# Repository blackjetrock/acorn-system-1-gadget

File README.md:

# Acorn System One Gadget

This is a small gadget that attaches to an Acorn System One. It is a Pico XL RP2350 with 48 GPIOs attached to the
expansion bus of the System One

* 60K of memory. The RP2350 emulates RAM everywhere in the memory space apart from block 0
* Tracing of addresses as code executes. This is a crude trace at the moment, but could be expanded.
* Loading of binary files from SD card into memory. For instance the monitor can be loaded from SD card and run from RAM.
* Snapshot of the entire 64K memory to an SD card file.
* A USB CLI that can drive the gadget
* An OLED display and three keys, these do nothing at the moment.
* Reset from the USB CLI
* Powering of the System One from the USB supply of the Pico. The regulator has to be removed for this to work. Power can
  come from a host computer if the USB CLI is used, or a battery power pack for portability.

On a system 1 you can load a slightly modified COS and BASIC into memory and run it:

The COS is modified to move the 6522 into RAM so that the keyboard can be driven from the USB CLI. The screen is captured by reading screen memory and also emulating som eof the functions of the 6845 CRT controller.

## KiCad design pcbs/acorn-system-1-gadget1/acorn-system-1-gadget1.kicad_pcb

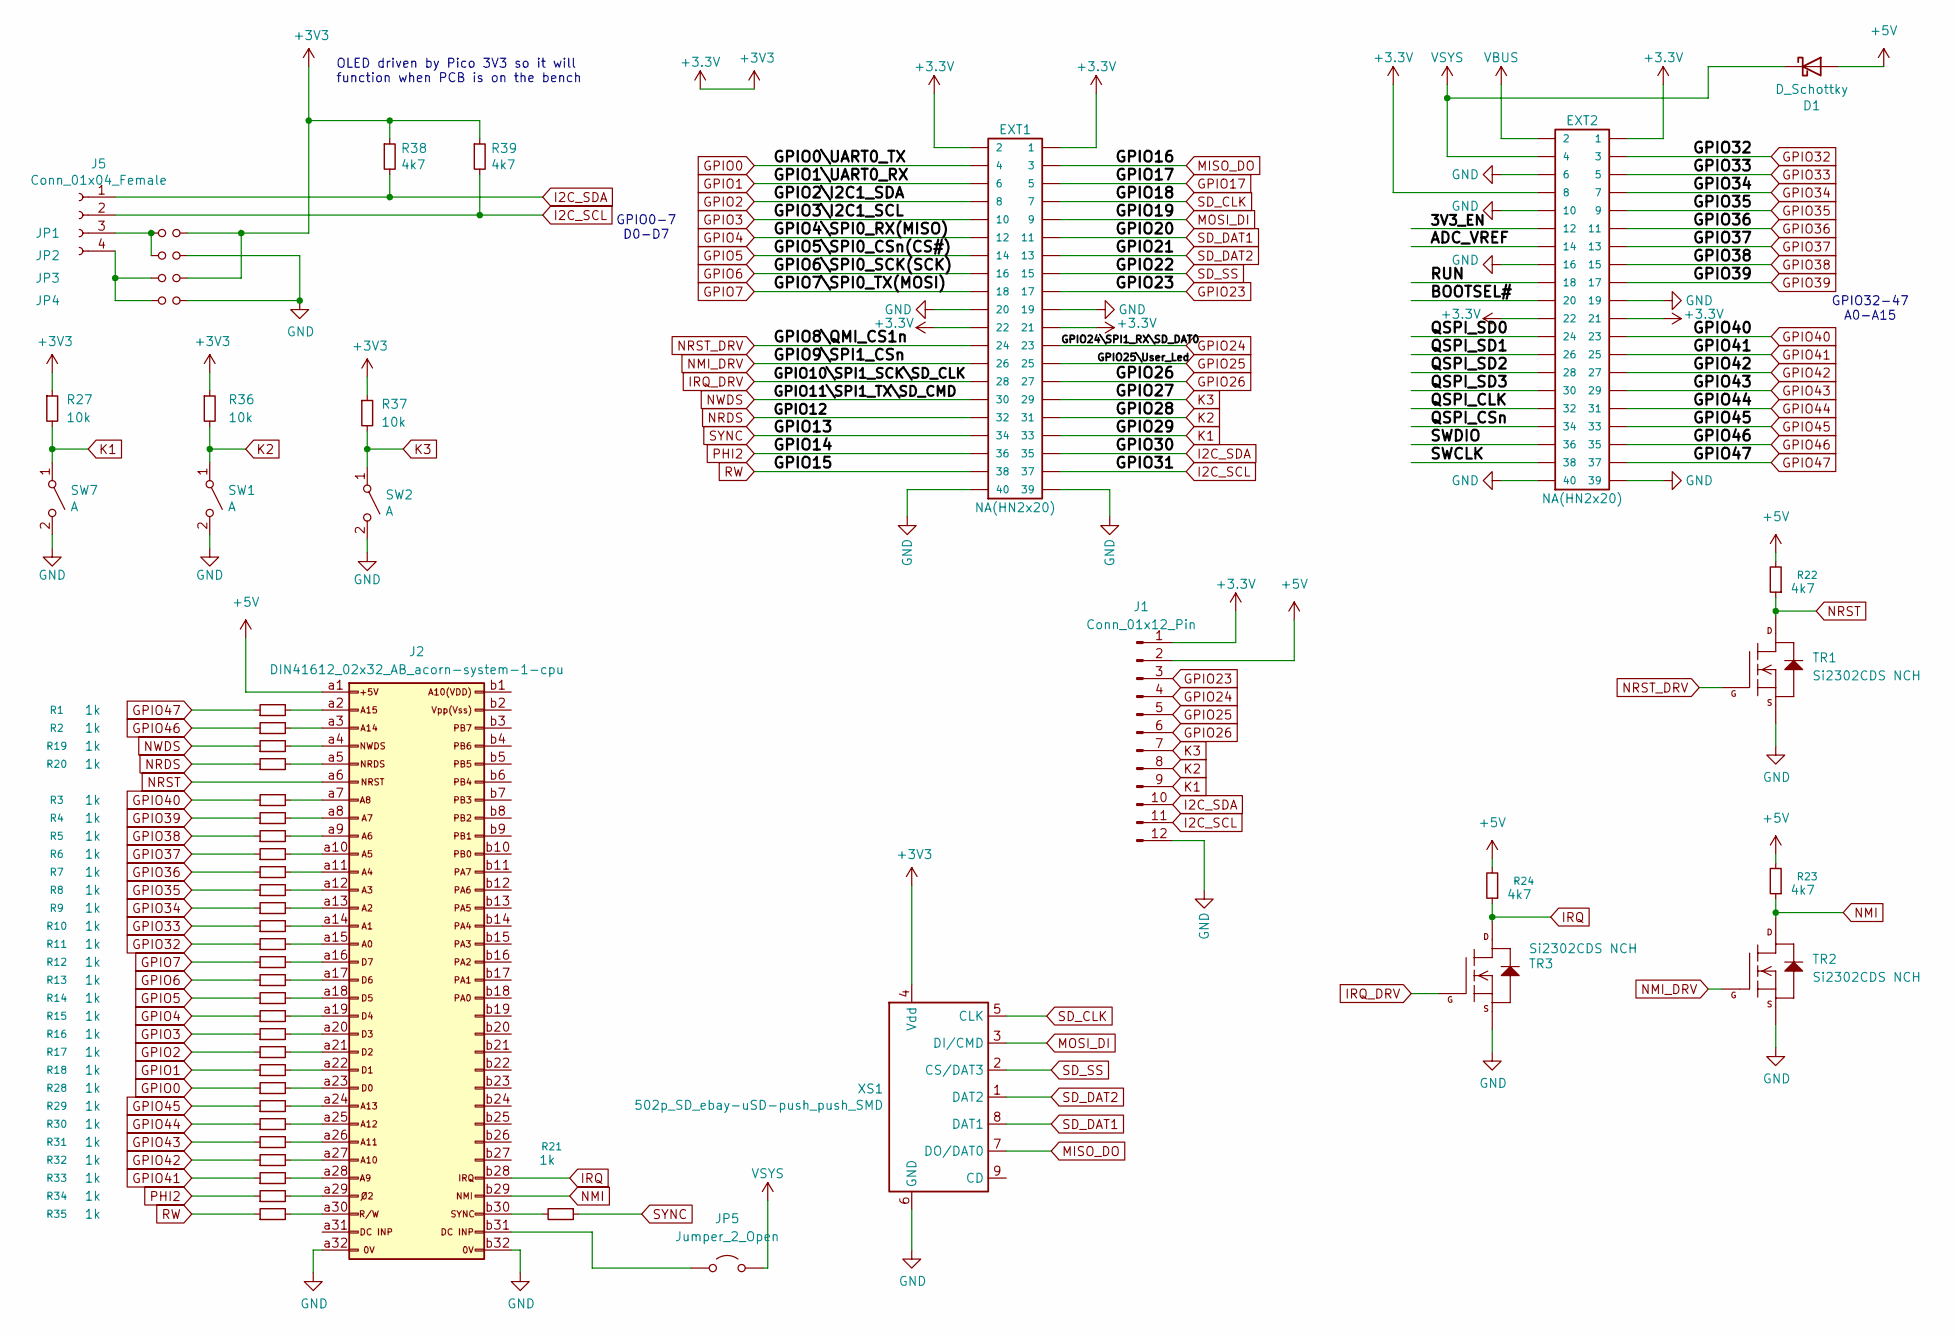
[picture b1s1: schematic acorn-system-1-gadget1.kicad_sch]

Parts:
D1: D_Schottky; D_SOD-123
EXT1, EXT2: NA(HN2x20); PinSocket_2x20_P2.54mm_Vertical
J1: Conn_01x12_Pin; PinHeader_1x12_P2.54mm_Vertical
J2: DIN41612_02x32_AB_acorn-system-1-cpu; DIN41612_Q_2x32_Female_Horizontal_THT
J5: Conn_01x04_Female; PinHeader_1x04_P2.54mm_Vertical
JP1, JP2, JP3, JP4: Jumper_NO_Small; SolderJumper-2_P1.3mm_Open_TrianglePad1.0x1.5mm
JP5: Jumper_2_Open; PinHeader_1x02_P2.54mm_Vertical
R1, R2, R3, R4, R5, R6, R7, R8, R9, R10, R11, R12, R13, R14, R15, R16, R17, R18, R19, R20, R21, R28, R29, R30, R31, R32, R33, R34, R35: 1k; R_0805_2012Metric_Pad1.20x1.40mm_HandSolder
R22, R23, R24, R38, R39: 4k7; R_0805_2012Metric_Pad1.20x1.40mm_HandSolder
R27, R36, R37: 10k; R_0805_2012Metric
SW1, SW2, SW7: A; SW_PUSH_6mm
TR1, TR2, TR3: Si2302CDS NCH; SOT-23
XS1: 502p_SD_ebay-uSD-push_push_SMD; Conn_uSDcard

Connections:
+3.3V: EXT1.1, EXT1.2, EXT1.21, EXT1.22, EXT2.1, EXT2.8, EXT2.21, EXT2.22, J1.1, JP1.2, JP3.2, R27.1, R36.1, R37.1, R38.1, R39.1, XS1.4 (Vdd)
+5V: D1.2 (A), J1.2, J2.a1, R22.2, R23.2, R24.2
/3V3_EN: EXT2.12
/ADC_VREF: EXT2.14
/BOOTSEL#: EXT2.20
/QSPI_CLK: EXT2.32
/QSPI_CSn: EXT2.34
/QSPI_SD0: EXT2.24
/QSPI_SD1: EXT2.26
/QSPI_SD2: EXT2.28
/QSPI_SD3: EXT2.30
/RUN: EXT2.18
/SWCLK: EXT2.38
/SWDIO: EXT2.36
GND: EXT1.19, EXT1.20, EXT1.39, EXT1.40, EXT2.6, EXT2.10, EXT2.16, EXT2.19, EXT2.39, EXT2.40, J1.12, J2.a32, J2.b32, JP2.2, JP4.2, SW1.2 (B), SW2.2 (B), SW7.2 (B), TR1.2 (S), TR2.2 (S), TR3.2 (S), XS1.6 (GND)
GPIO0: EXT1.4, R28.1
GPIO1: EXT1.6, R18.1
GPIO2: EXT1.8, R17.1
GPIO3: EXT1.10, R16.1
GPIO4: EXT1.12, R15.1
GPIO5: EXT1.14, R14.1
GPIO6: EXT1.16, R13.1
GPIO7: EXT1.18, R12.1
GPIO17: EXT1.5
GPIO23: EXT1.17, J1.3
GPIO24: EXT1.23, J1.4
GPIO25: EXT1.25, J1.5
GPIO26: EXT1.27, J1.6
GPIO32: EXT2.3, R11.1
GPIO33: EXT2.5, R10.1
GPIO34: EXT2.7, R9.1
GPIO35: EXT2.9, R8.1
GPIO36: EXT2.11, R7.1
GPIO37: EXT2.13, R6.1
GPIO38: EXT2.15, R5.1
GPIO39: EXT2.17, R4.1
GPIO40: EXT2.23, R3.1
GPIO41: EXT2.25, R33.1
GPIO42: EXT2.27, R32.1
GPIO43: EXT2.29, R31.1
GPIO44: EXT2.31, R30.1
GPIO45: EXT2.33, R29.1
GPIO46: EXT2.35, R2.1
GPIO47: EXT2.37, R1.1
I2C_SCL: EXT1.37, J1.11, J5.2, R39.2
I2C_SDA: EXT1.35, J1.10, J5.1, R38.2
IRQ: J2.b28, R24.1, TR3.3 (D)
IRQ_DRV: EXT1.28, TR3.1 (G)
K1: EXT1.33, J1.9, R27.2, SW7.1 (A)
K2: EXT1.31, J1.8, R36.2, SW1.1 (A)
K3: EXT1.29, J1.7, R37.2, SW2.1 (A)
MISO_DO: EXT1.3, XS1.7 (DO/DAT0)
MOSI_DI: EXT1.9, XS1.3 (DI/CMD)
NMI: J2.b29, R23.1, TR2.3 (D)
NMI_DRV: EXT1.26, TR2.1 (G)
NRDS: EXT1.32, R20.1
NRST: J2.a6, R22.1, TR1.3 (D)
NRST_DRV: EXT1.24, TR1.1 (G)
NWDS: EXT1.30, R19.1
unnamed: J2.a2, R1.2
unnamed: J2.a3, R2.2
unnamed: J2.a4, R19.2
unnamed: J2.a5, R20.2
unnamed: J2.a7, R3.2
unnamed: J2.a8, R4.2
unnamed: J2.a9, R5.2
unnamed: J2.a10, R6.2
unnamed: J2.a11, R7.2
unnamed: J2.a12, R8.2
unnamed: J2.a13, R9.2
unnamed: J2.a14, R10.2
unnamed: J2.a15, R11.2
unnamed: J2.a16, R12.2
unnamed: J2.a17, R13.2
unnamed: J2.a18, R14.2
unnamed: J2.a19, R15.2
unnamed: J2.a20, R16.2
unnamed: J2.a21, R17.2
unnamed: J2.a22, R18.2
unnamed: J2.a23, R28.2
unnamed: J2.a24, R29.2
unnamed: J2.a25, R30.2
unnamed: J2.a26, R31.2
unnamed: J2.a27, R32.2
unnamed: J2.a28, R33.2
unnamed: J2.a29, R34.2
unnamed: J2.a30, R35.2
unnamed: J2.b30, R21.2
unnamed: J2.b31, JP5.1 (A)
unnamed: J5.3, JP1.1, JP2.1
unnamed: J5.4, JP3.1, JP4.1
PHI2: EXT1.36, R34.1
RW: EXT1.38, R35.1
SD_CLK: EXT1.7, XS1.5 (CLK)
SD_DAT1: EXT1.11, XS1.8 (DAT1)
SD_DAT2: EXT1.13, XS1.1 (DAT2)
SD_SS: EXT1.15, XS1.2 (CS/DAT3)
SYNC: EXT1.34, R21.1
VBUS: EXT2.2
VSYS: D1.1 (K), EXT2.4, JP5.2 (B)

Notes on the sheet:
OLED driven by Pico 3V3 so it will function when PCB is on the bench
GPIO0-7 D0-D7
GPIO32-47 A0-A15

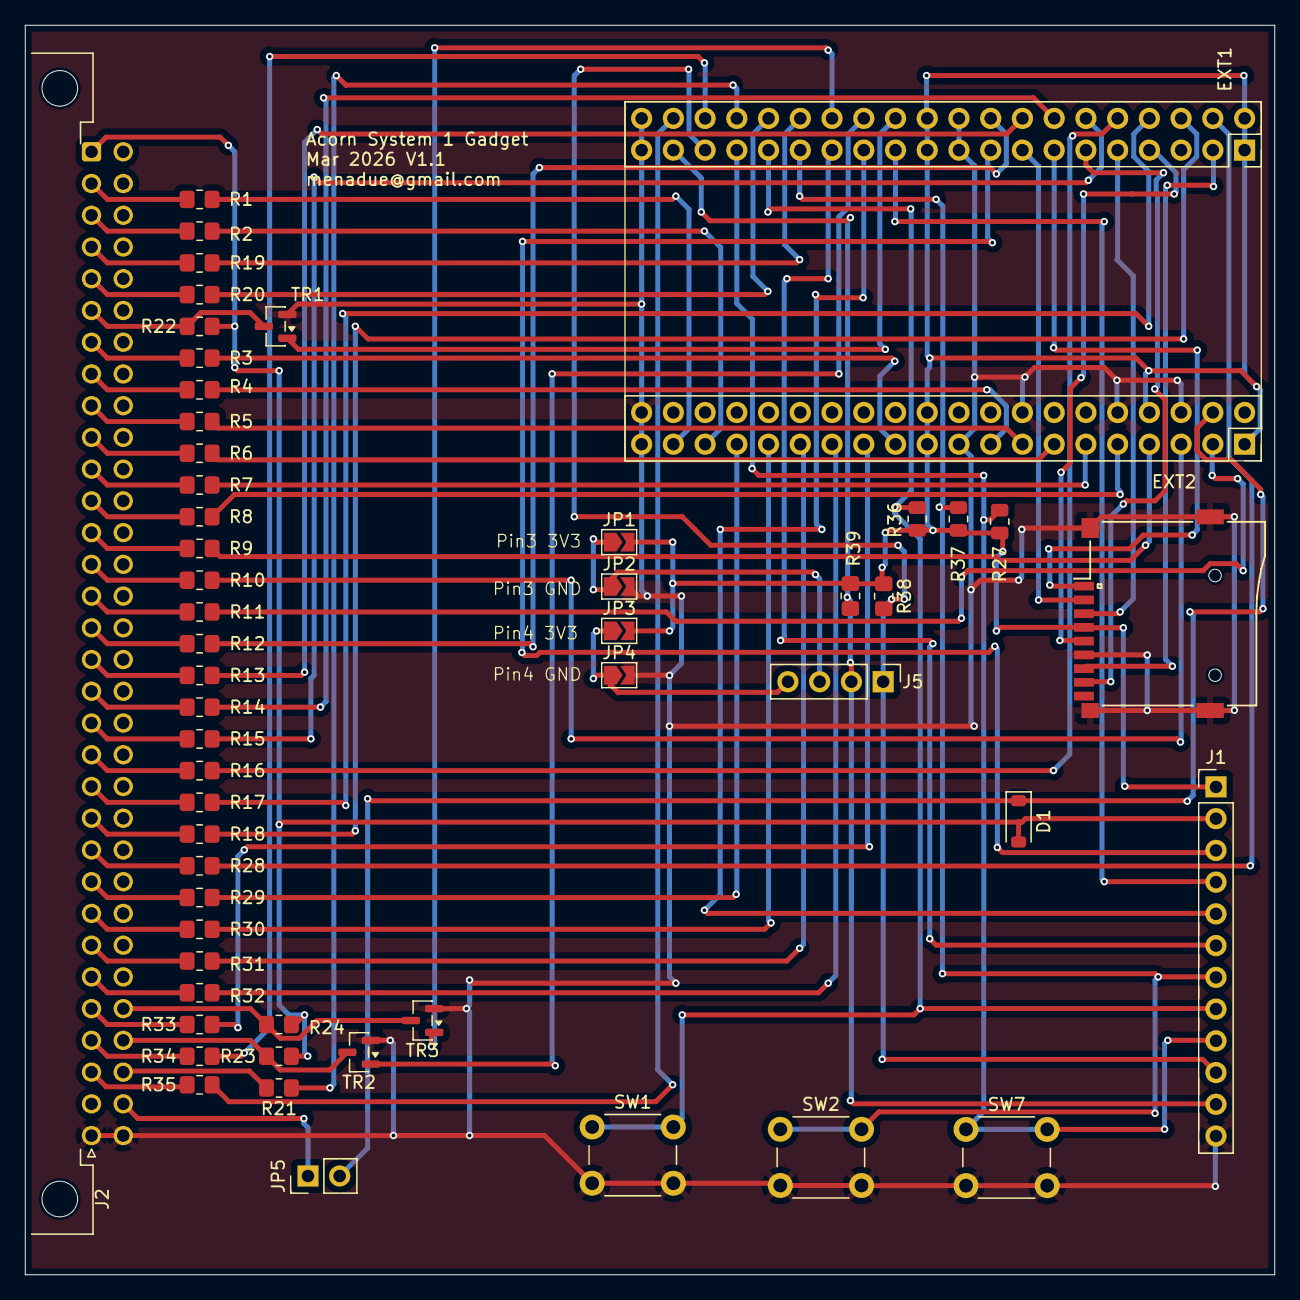
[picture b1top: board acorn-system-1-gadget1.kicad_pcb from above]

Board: 2 copper layers, 100.0 x 100.0 mm, 55 parts (0 on the bottom side), 86 nets.

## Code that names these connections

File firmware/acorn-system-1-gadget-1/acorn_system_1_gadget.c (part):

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const int PIN_D6        =  6;
const int PIN_D7        =  7;

const int PIN_NRST_DRV  =  8;
const int PIN_NMI_DRV   =  9;
const int PIN_IRQ_DRV   =  10;
const int PIN_NWDS      =  11;
const int PIN_NRDS      =  12;
const int PIN_SYNC      =  13;
const int PIN_PHI2      =  14;
const int PIN_RW        =  15;

#define PIN_BITNUM_NWDS    11
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void cli_do_reset(void)
{
  printf("\nResetting...");
  gpio_put(PIN_NRST_DRV, 1);
  sleep_ms(50);
  gpio_put(PIN_NRST_DRV, 0);

  printf("\nDone");
  
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
#define USB_FLAGS 0

#define RW_MASK (( 1<< PIN_NWDS) | ( 1<< PIN_NRDS))
#define RD_MASK  ( 1<< PIN_NRDS)
#define WR_MASK  ( 1<< PIN_NWDS)


// 16K from 0x8000
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  set_gpio_input(PIN_D6);
  set_gpio_input(PIN_D7);
  
  set_gpio_output(PIN_NRST_DRV);
  set_gpio_output(PIN_NMI_DRV);
  set_gpio_output(PIN_IRQ_DRV);
  set_gpio_input(PIN_NWDS);
  set_gpio_input(PIN_NRDS);
  set_gpio_input(PIN_SYNC);
  set_gpio_input(PIN_PHI2);
  set_gpio_input(PIN_RW);

  // SD card GPIOs here
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  
  // Set outputs to safe levels
  
  gpio_put(PIN_NRST_DRV, 0);
  gpio_put(PIN_NMI_DRV, 0);
  gpio_put(PIN_IRQ_DRV, 0);
  
  ////////////////////////////////////////////////////////////////////////////////
  //
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
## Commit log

2026-02-28 "Update"
2026-03-13 Shadow of memory works in RAM. PROM not as good?
2026-03-14 Reads and writes a block of 256 bytes at 0xB000
2026-03-14 Emulates RAM and has acorn 1 app built in
2026-03-19 Emulation OK, can read from SD card and snapshot all memory back
2026-03-29 Enhance README with gadget description and features
    Expanded the README with detailed gadget features and functionality.
2026-03-29 Update README with COS and BASIC loading instructions
    Added information about loading modified COS and BASIC into memory on System One.
